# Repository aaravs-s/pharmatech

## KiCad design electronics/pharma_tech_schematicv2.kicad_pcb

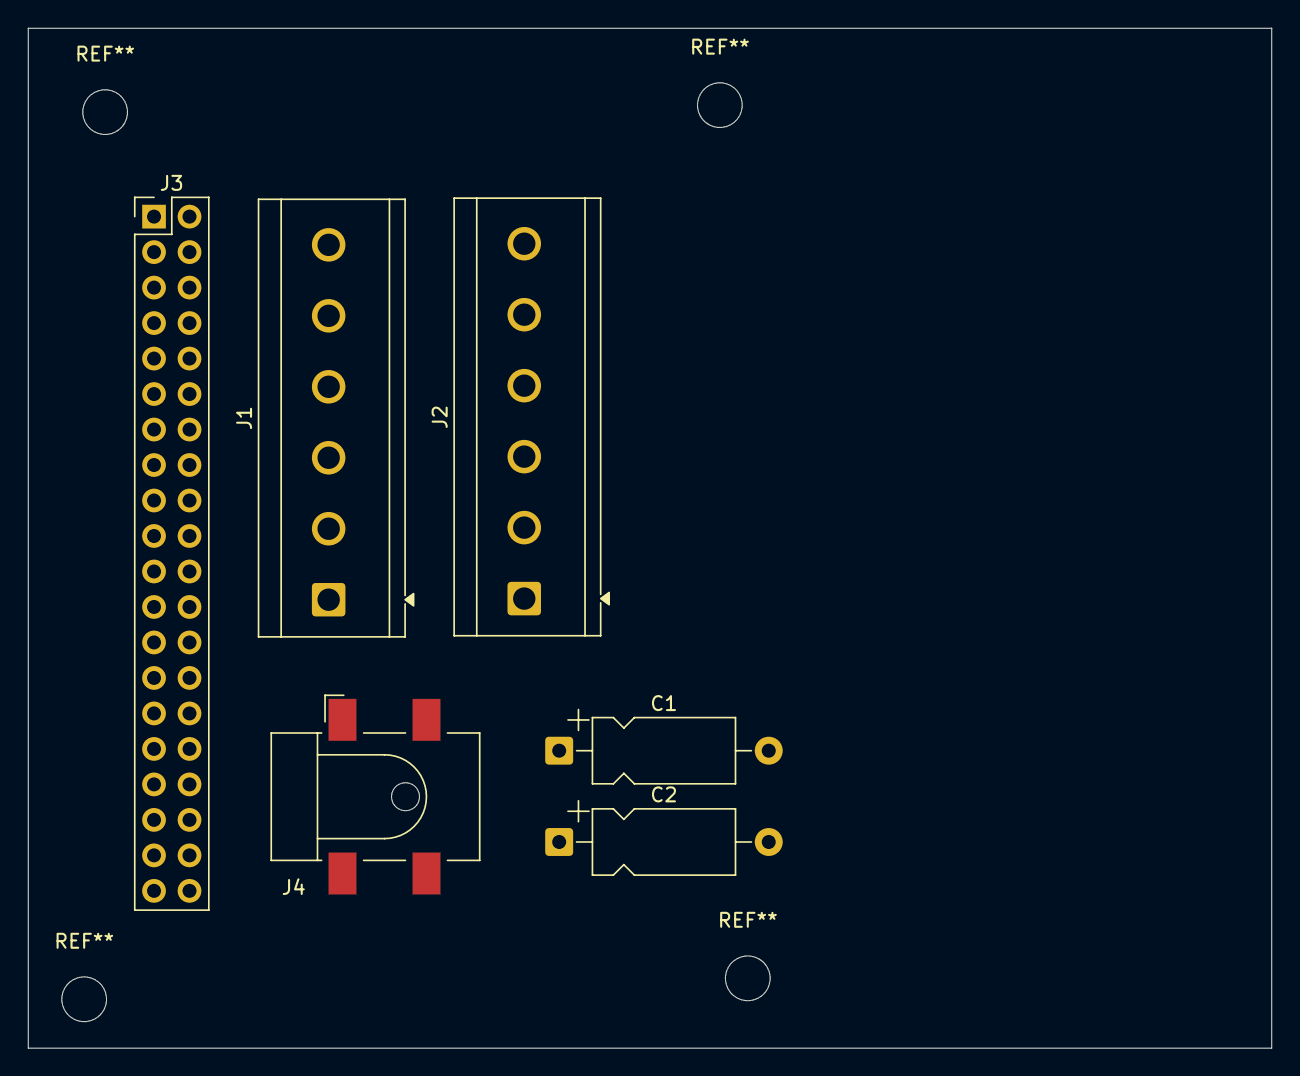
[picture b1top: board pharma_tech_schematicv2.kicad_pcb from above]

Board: 2 copper layers, 89.0 x 73.0 mm, 6 parts (0 on the bottom side), 6 nets, no tracks yet.

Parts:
C1, C2: C; CP_Axial_L10.0mm_D4.5mm_P15.00mm_Horizontal
J1: MOTOR1; TerminalBlock_CUI_TB007-508-06_1x06_P5.08mm_Horizontal
J2: MOTOR2; TerminalBlock_CUI_TB007-508-06_1x06_P5.08mm_Horizontal
J3: RASPBERRY_PI_4; PinHeader_2x20_P2.54mm_Vertical
J4: Barrel_Jack_MountingPin; BarrelJack_CLIFF_FC681465S_SMT_Horizontal

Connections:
+5V: C2.1, J3.2
+24V: C1.1, J1.5, J2.5, J4.1
/DIR1: J1.3, J2.4, J3.5, J3.15
/ENA1: J1.4, J2.3, J3.7, J3.13
/PLS1 (STEP): J1.2, J2.2, J3.3, J3.11
GND: C1.2, C2.2, J1.1, J1.6, J2.1, J2.6, J4.2
